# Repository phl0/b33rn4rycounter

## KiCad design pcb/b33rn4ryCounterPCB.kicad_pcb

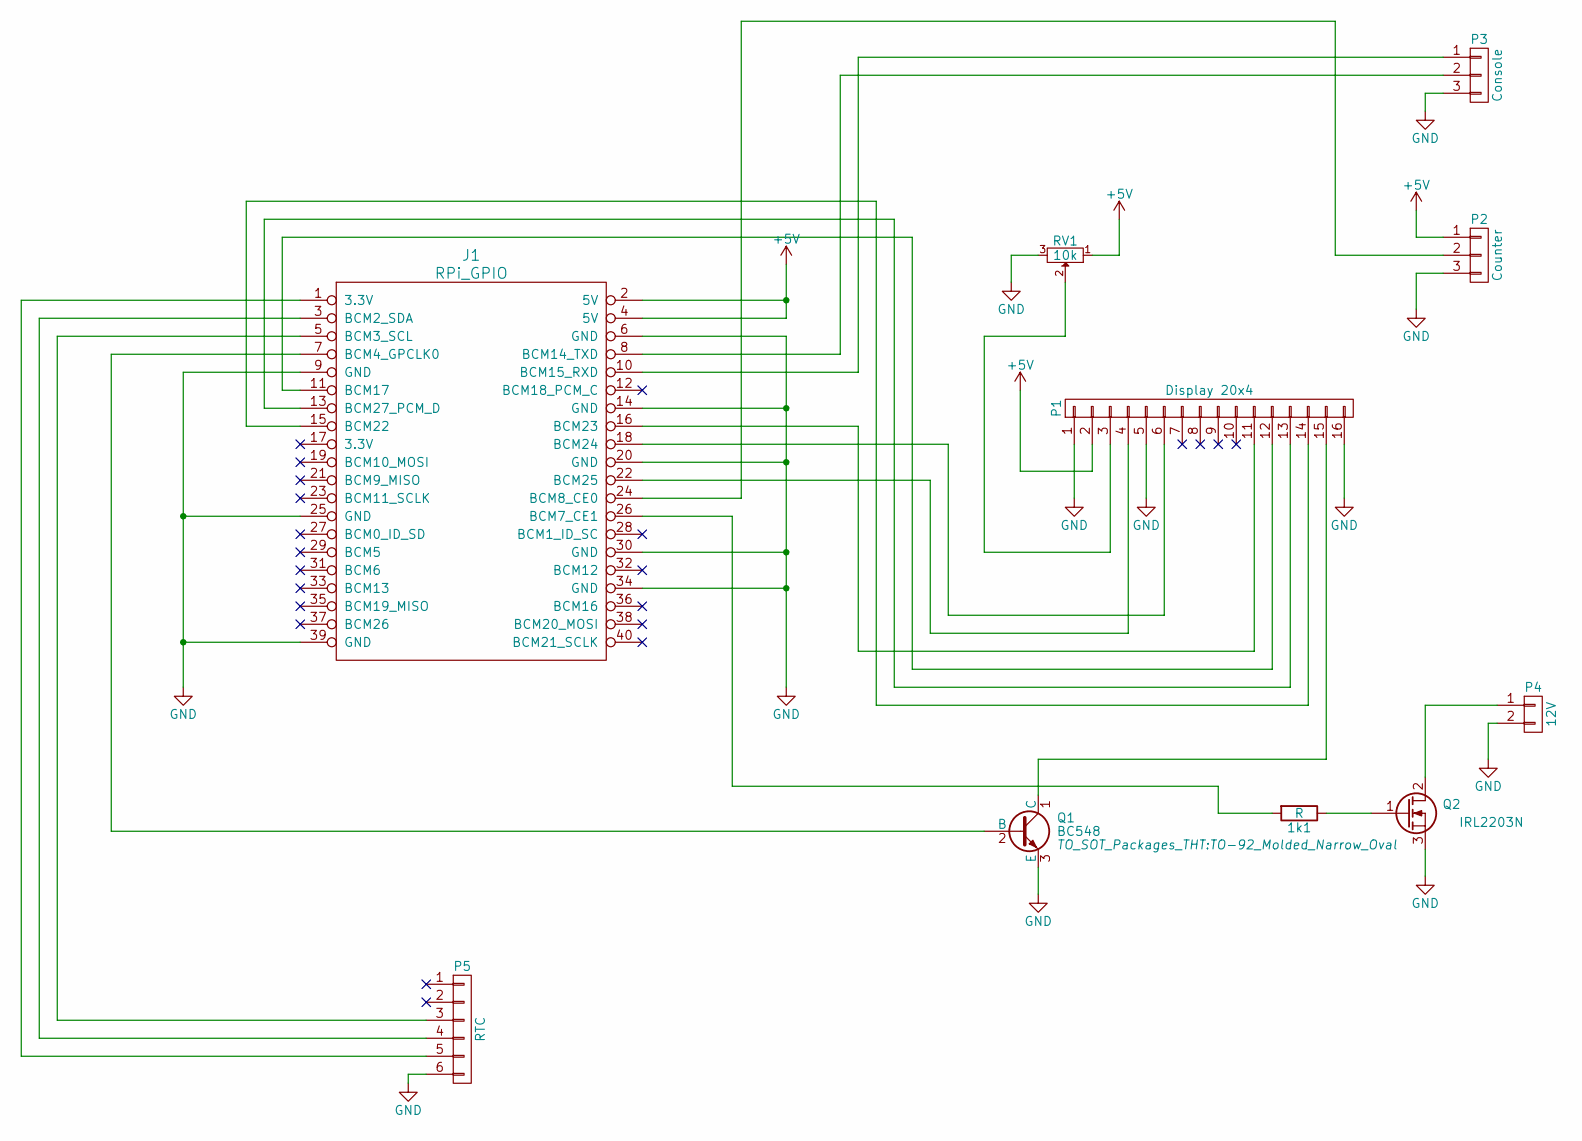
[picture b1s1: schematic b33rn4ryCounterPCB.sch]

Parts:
1k1: R; Resistor_Horizontal_RM7mm
J1: RPi_GPIO; Pin_Header_Straight_2x20
P1: Display 20x4; Pin_Header_Angled_1x16
P2: Counter; Pin_Header_Straight_1x03
P3: Console; Pin_Header_Straight_1x03
P4: 12V; Pin_Header_Straight_1x02
P5: RTC; Pin_Header_Straight_1x06
Q1: BC548; TO-92_Molded_Narrow_Oval
Q2: IRL2203N; TO-220_Neutral123_Horizontal
RV1: 10k; Potentiometer_Bourns_3339P_Angular_ScrewUp

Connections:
+5V: J1.2 (5V), J1.4 (5V), P1.2, P2.1, RV1.1
GND: J1.6 (GND), J1.9 (GND), J1.14 (GND), J1.20 (GND), J1.25 (GND), J1.30 (GND), J1.34 (GND), J1.39 (GND), P1.1, P1.5, P1.16, P2.3, P3.3, P4.2, P5.6, Q1.3 (E), Q2.3 (S), RV1.3
unnamed: 1k1.1, Q2.1 (G)
unnamed: 1k1.2, J1.26 (BCM7_CE1)
unnamed: J1.1 (3.3V), P5.5
unnamed: J1.3 (BCM2_SDA), P5.4
unnamed: J1.5 (BCM3_SCL), P5.3
unnamed: J1.7 (BCM4_GPCLK0), Q1.2 (B)
unnamed: J1.8 (BCM14_TXD), P3.2
unnamed: J1.10 (BCM15_RXD), P3.1
unnamed: J1.11 (BCM17), P1.12
unnamed: J1.13 (BCM27_PCM_D), P1.13
unnamed: J1.15 (BCM22), P1.14
unnamed: J1.16 (BCM23), P1.11
unnamed: J1.18 (BCM24), P1.6
unnamed: J1.22 (BCM25), P1.4
unnamed: J1.24 (BCM8_CE0), P2.2
unnamed: P1.3, RV1.2
unnamed: P1.15, Q1.1 (C)
unnamed: P4.1, Q2.2 (D)

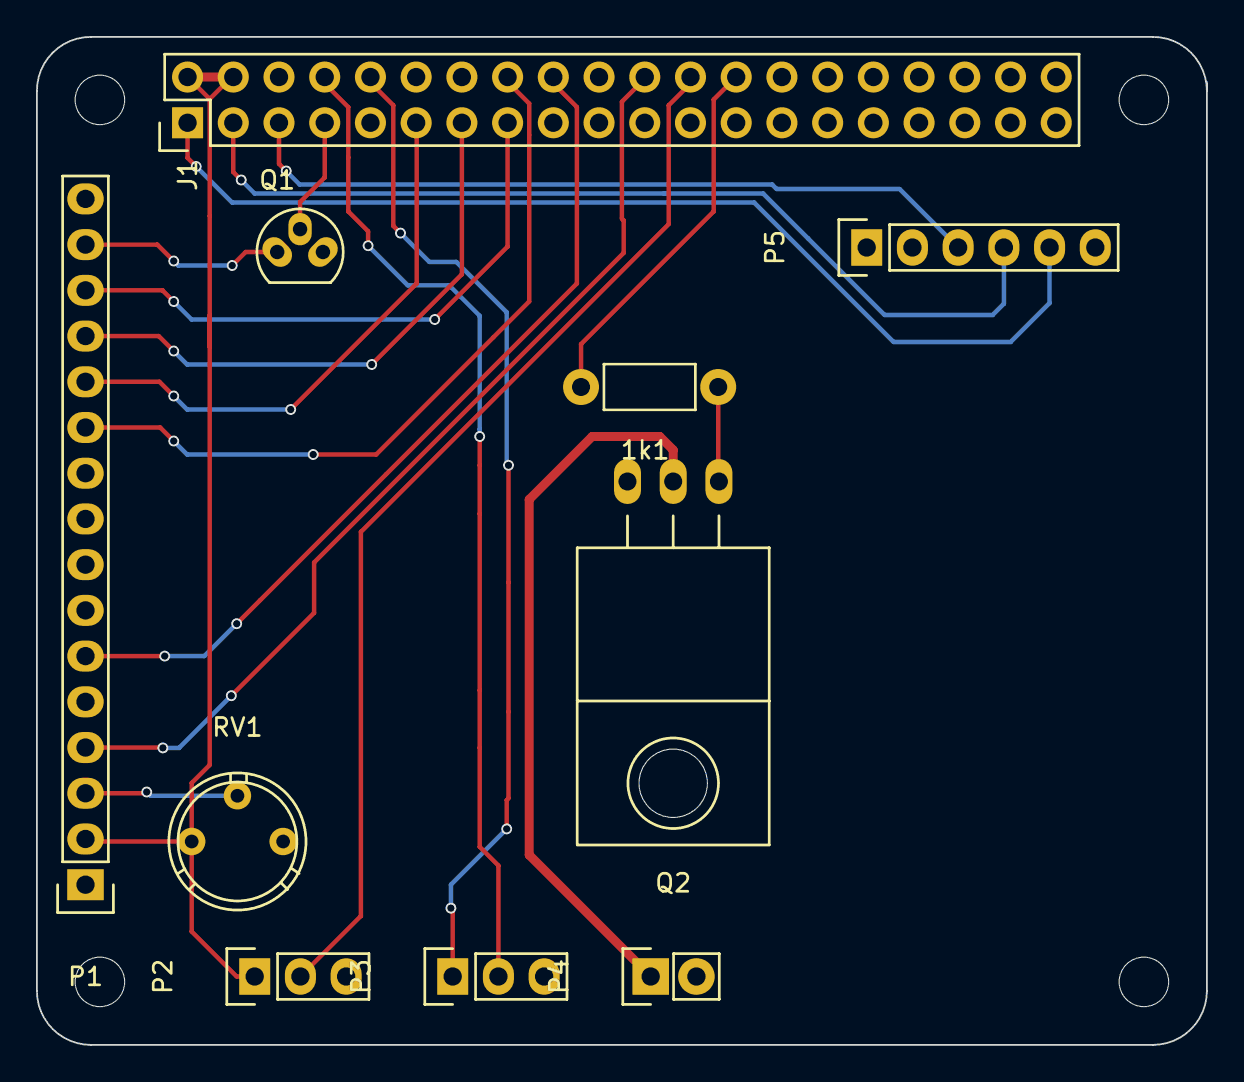
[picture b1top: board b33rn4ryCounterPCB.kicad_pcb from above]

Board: 2 copper layers, 65.0 x 56.0 mm, 10 parts (0 on the bottom side), 20 nets.

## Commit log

2017-08-14 Add 1st draft of PCB
2017-08-14 Add README
2017-08-15 Add 1N5000 diode
2019-08-20 B33rn4ryReader: serial-reader: disable checksum-check
2019-08-20 B33rn4ryReader: keep reading "startbyte" for serial-reader
    To be compatible with the data read by UsbReader
2019-08-21 B33rn4ryReader: add "2" prefix for serial-reader
    add this prefix to the tagdata, as it matches the data we have currently stored in the database.
2019-08-21 B33rn4ryExceptions: create InvalidRfidReading
2019-08-21 handle invalid readings
    sometimes an invalid / inclomplete rfid is read.
    handle this be rasing a InvalidRfidReading exception
2019-08-21 stop pulsuig of relais (very hackish)
    As we often have invalid-readings and Null-readings
    in between a single read of a tag, the valve gets
    closed for short during a "session".
